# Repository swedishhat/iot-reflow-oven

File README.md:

# iot-reflow-oven
DIY solder reflow ovens. Internet of Toasters. So hot right now.

## Branches

### master
This is where milestone-level code lives. A rule of thumb is that it will always be behind or equal to __dev__ branch. I generally merge changes into master after each documentation article is published

### dev
This is where the action is. I try to make sane commits but continue with caution... thar be dragons.

## Folder Hierarchy

### [doc] Documentation Files
* __01_triac-dimmer__: [Control Your AC Mains with a Microcontroller](http://www.allaboutcircuits.com/projects/controlling-ac-mains-with-a-microcontroller-for-fun-and-profit/)
* __02_atmega-controller__: [Designing Your Own Controller for a Solder Reflow Oven](http://www.allaboutcircuits.com/projects/designing-the-controller-for-a-diy-solder-reflow-oven/)

### [sw] Software Files

#### atmega328p
C files and headers for oven controller

#### esp8266
Either Arduino or NodeMCU files for the controller's web interface

#### python
Scripts for viewing, logging, and interacting with serial data from oven controller

### [hw] Hardware Files

#### most-toast-controller
Contest entry for [Hackaday's](http://hackaday.com/) [Square Inch Project Challenge](http://hackaday.com/2015/10/02/the-square-inch-project-challenges-your-layout-skills/). Small KiCad board containing ATmega328P, MAX31855, headers for ESP-01, thermocouple connector, voltage regulator, and header for CR2032 battery module.

####triac-dimmer
KiCad files for the TRIAC, TRIAC driver circuit, and zero cross detector.

## Attributions
A good chunk of the ATmega328P was modeled after Andy Brown's Bluetooth enabled reflow oven controller. He used and ATmega8 and wrote his project in C++ but a lot of the code is maps pretty easily to C on an ATmega328P. His tutorial page is located [here](http://andybrown.me.uk/2015/07/12/awreflow2/) and his GitHub repository is located [here](https://github.com/andysworkshop/awreflow2/)

The UART code for the ATmega328P was taken from a library writen by [Andy Gock](https://github.com/andygock/avr-uart). It has the added benefit of being generic across numerous AVR platforms and supports multiple UARTs. The library itself contains code from Peter Fleury and others. Andy's license information can be found [here](https://github.com/andygock/avr-uart/blob/master/LICENSE.txt) and there is more complete information located in the uart.h file.

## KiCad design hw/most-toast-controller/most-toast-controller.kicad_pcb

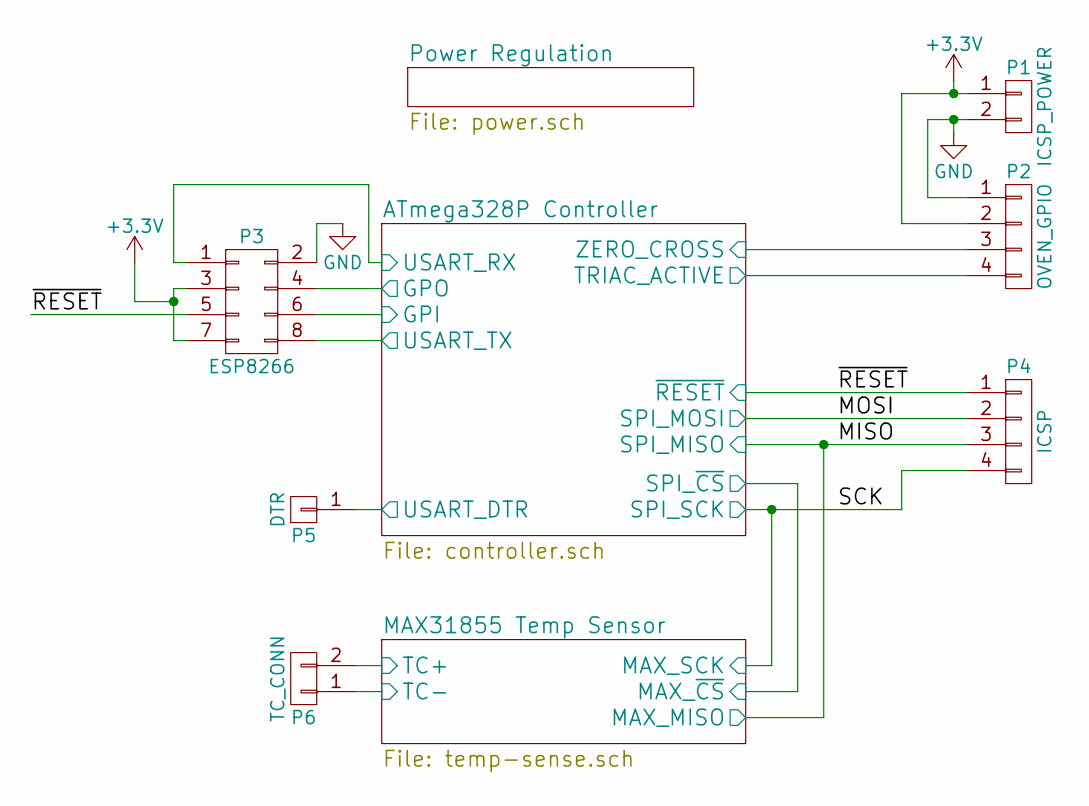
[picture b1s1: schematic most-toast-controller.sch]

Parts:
P1: ICSP_POWER; Pin_Header_Straight_1x02
P2: OVEN_GPIO; Pin_Header_Straight_1x04
P3: ESP8266; Pin_Header_Straight_2x04
P4: ICSP; Pin_Header_Straight_1x04
P5: DTR; Pin_Header_Straight_1x01
P6: TC_CONN; OSTTE020104

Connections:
+3V3: P1.1, P2.2, P3.3, P3.7; also elsewhere on the board
/ATmega328P Controller/GPI: P3.6; also elsewhere on the board
/ATmega328P Controller/GPO: P3.4; also elsewhere on the board
/ATmega328P Controller/SPI_MOSI: P4.2; also elsewhere on the board
/ATmega328P Controller/TRIAC_ACTIVE: P2.4; also elsewhere on the board
/ATmega328P Controller/USART_DTR: P5.1; also elsewhere on the board
/ATmega328P Controller/USART_RX: P3.1; also elsewhere on the board
/ATmega328P Controller/USART_TX: P3.8; also elsewhere on the board
/ATmega328P Controller/ZERO_CROSS: P2.3; also elsewhere on the board
/ATmega328P Controller/~RESET: P3.5, P4.1; also elsewhere on the board
/MAX31855 Temp Sensor/MAX_MISO: P4.3; also elsewhere on the board
/MAX31855 Temp Sensor/MAX_SCK: P4.4; also elsewhere on the board
/MAX31855 Temp Sensor/TC+: P6.2; also elsewhere on the board
/MAX31855 Temp Sensor/TC-: P6.1; also elsewhere on the board
GND: P1.2, P2.1, P3.2; also elsewhere on the board

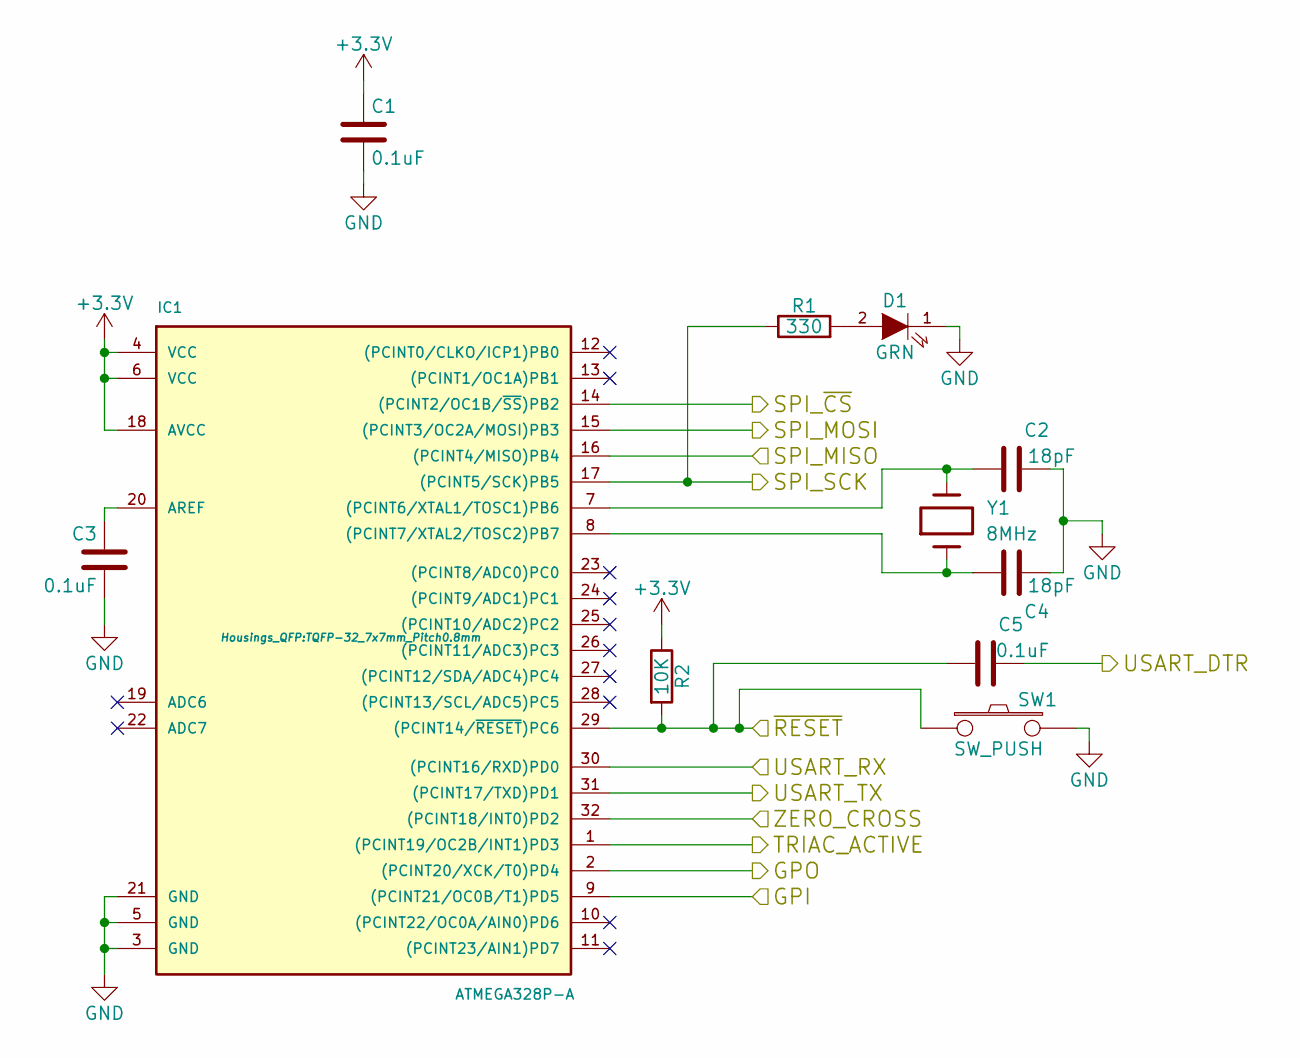
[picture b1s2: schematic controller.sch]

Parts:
C1, C3, C5: 0.1uF; C_0805_HandSoldering
C2, C4: 18pF; C_0805_HandSoldering
D1: GRN; R_0805_HandSoldering
IC1: ATMEGA328P-A; TQFP-32_7x7mm_Pitch0.8mm
R1: 330; R_0805_HandSoldering
R2: 10K; R_0805_HandSoldering
SW1: SW_PUSH; SW_SPST_FSMSM
Y1: 8MHz; Crystal_HC49-SD_SMD

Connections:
+3V3: C1.1, IC1.4 (VCC), IC1.6 (VCC), IC1.18 (AVCC), R2.1; also elsewhere on the board
/ATmega328P Controller/GPI: IC1.9 ((PCINT21/OC0B/T1)PD5); also elsewhere on the board
/ATmega328P Controller/GPO: IC1.2 ((PCINT20/XCK/T0)PD4); also elsewhere on the board
/ATmega328P Controller/SPI_MOSI: IC1.15 ((PCINT3/OC2A/MOSI)PB3); also elsewhere on the board
/ATmega328P Controller/TRIAC_ACTIVE: IC1.1 ((PCINT19/OC2B/INT1)PD3); also elsewhere on the board
/ATmega328P Controller/USART_DTR: C5.2; also elsewhere on the board
/ATmega328P Controller/USART_RX: IC1.30 ((PCINT16/RXD)PD0); also elsewhere on the board
/ATmega328P Controller/USART_TX: IC1.31 ((PCINT17/TXD)PD1); also elsewhere on the board
/ATmega328P Controller/ZERO_CROSS: IC1.32 ((PCINT18/INT0)PD2); also elsewhere on the board
/ATmega328P Controller/~RESET: C5.1, IC1.29 ((PCINT14/~RESET~)PC6), R2.2, SW1.1; also elsewhere on the board
/MAX31855 Temp Sensor/MAX_MISO: IC1.16 ((PCINT4/MISO)PB4); also elsewhere on the board
/MAX31855 Temp Sensor/MAX_SCK: IC1.17 ((PCINT5/SCK)PB5), R1.1; also elsewhere on the board
/MAX31855 Temp Sensor/MAX_~CS: IC1.14 ((PCINT2/OC1B/~SS~)PB2); also elsewhere on the board
GND: C1.2, C2.2, C3.2, C4.2, D1.1 (K), IC1.3 (GND), IC1.5 (GND), IC1.21 (GND), SW1.2; also elsewhere on the board
unnamed: C2.1, IC1.7 ((PCINT6/XTAL1/TOSC1)PB6), Y1.2
unnamed: C3.1, IC1.20 (AREF)
unnamed: C4.1, IC1.8 ((PCINT7/XTAL2/TOSC2)PB7), Y1.1
unnamed: D1.2 (A), R1.2

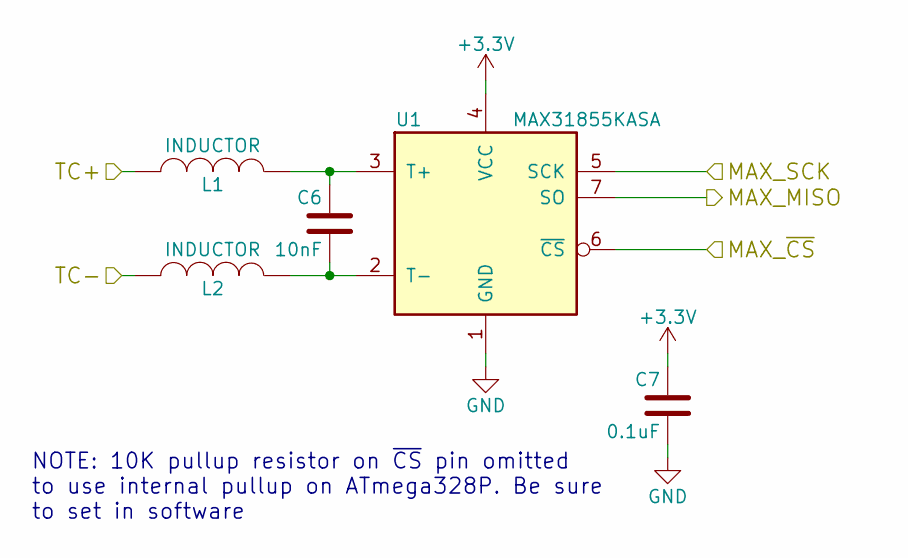
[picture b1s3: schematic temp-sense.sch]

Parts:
C6: 10nF; C_0805_HandSoldering
C7: 0.1uF; C_0805_HandSoldering
L1, L2: INDUCTOR; C_0805_HandSoldering
U1: MAX31855KASA; SOIC-8_3.9x4.9mm_Pitch1.27mm

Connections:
+3V3: C7.1, U1.4 (VCC); also elsewhere on the board
/MAX31855 Temp Sensor/MAX_MISO: U1.7 (SO); also elsewhere on the board
/MAX31855 Temp Sensor/MAX_SCK: U1.5 (SCK); also elsewhere on the board
/MAX31855 Temp Sensor/MAX_~CS: U1.6 (~CS~); also elsewhere on the board
/MAX31855 Temp Sensor/TC+: L1.2; also elsewhere on the board
/MAX31855 Temp Sensor/TC-: L2.2; also elsewhere on the board
GND: C7.2, U1.1 (GND); also elsewhere on the board
unnamed: C6.1, L1.1, U1.3 (T+)
unnamed: C6.2, L2.1, U1.2 (T-)

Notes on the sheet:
NOTE: 10K pullup resistor on ~CS~ pin omitted to use internal pullup on ATmega328P. Be sure to set in software

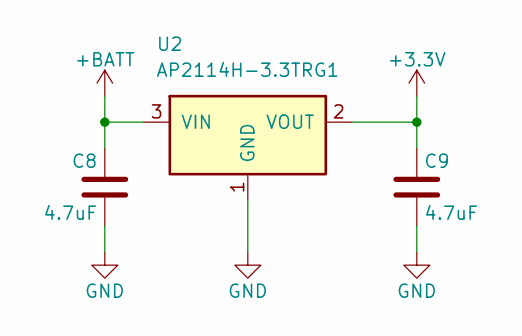
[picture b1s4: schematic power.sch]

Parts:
C8, C9: 4.7uF; C_0805_HandSoldering
U2: AP2114H-3.3TRG1; SOT-223

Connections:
+3V3: C9.1, U2.2 (VOUT); also elsewhere on the board
+BATT: C8.1, U2.3 (VIN)
GND: C8.2, C9.2, U2.1 (GND); also elsewhere on the board

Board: 2 copper layers, 25 parts (5 on the bottom side), 23 nets, no tracks yet.

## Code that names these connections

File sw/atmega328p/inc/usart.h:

// usart.h
#ifndef _USART_H
#define _USART_H

#define USART_BAUD      9600
#define BAUD_PRESCALE   ((((F_CPU / 16) + (USART_BAUD / 2)) / (USART_BAUD)) - 1)      

#define USART_TX        PD1
#define USART_TX_PORT   PORTD
#define USART_TX_DDR    DDRD
#define USART_TX_PIN    PIND

#define USART_RX        PD0
#define USART_RX_PORT   PORTD
#define USART_RX_DDR    DDRD
#define USART_RX_PIN    PIND

/*** USART Initialization Function ***/
void usart_setup(uint32_t ubrr);

/*** USART Flush Function ***/
void usart_flush(void);

/*** USART Transmit Byte Function ***/
void usart_txb(const char data);

/*** USART Print String Function ***/
void usart_print (const char *data);

/*** USART Print String Function with New Line and Carriage Return ***/
void usart_println (const char *data);

#endif

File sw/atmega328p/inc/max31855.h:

/*** max31855.h ***/

#ifndef _MAX31855_H_
#define _MAX31855_H_

/*** GPIO Definitions ***/
#define MAX31855_CS             PB2
#define MAX31855_CS_PORT        PORTB
#define MAX31855_CS_DDR         DDRB
#define MAX31855_CS_PIN         PINB

#define MAX31855_MOSI           PB3
#define MAX31855_MOSI_PORT      PORTB
#define MAX31855_MOSI_DDR       DDRB
#define MAX31855_MOSI_PIN       PINB

#define MAX31855_MISO           PB4
#define MAX31855_MISO_PORT      PORTB
#define MAX31855_MISO_DDR       DDRB
#define MAX31855_MISO_PIN       PINB

#define MAX31855_SCK            PB5
#define MAX31855_SCK_PORT       PORTB
#define MAX31855_SCK_DDR        DDRB
#define MAX31855_SCK_PIN        PINB

/*** Constants ***/
// Status Definitions
#define UNKNOWN                 0
#define OK                      1
#define SCV_FAULT               2
#define SCG_FAULT               3
#define OC_FAULT                4

#define DEFAULT_POLL_INTERVAL   1000    // Read temp probe every second

/*** MAX31855 Device Struct ***/
typedef struct max31855
{
    int16_t     extTemp;        // 14-bit TC temp
    int16_t     intTemp;        // 12-bit internal temp
    uint8_t     status;         // Status flags
    uint32_t    lastTempTime;   // "Timestamp"
    uint32_t    pollInterval;   // Refresh rate of sensor
} max31855;


/*** Temperature Sensor "Object" Constructor ***/
max31855 *max31855_setup(void);

/*** Temperature Sensor Printing Function ***/
void max31855_print(max31855 *tempSense);

/*** Read and Update Temperature Sensor Function ***/
bool max31855_readTempDone(max31855 *tempSense);

/*** Status Message Helper Function ***/
const char *max31855_statusString(uint8_t status);
#endif

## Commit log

2015-11-05 First! Created folder hierarchy and added schems / first round of C code :tada:
2015-11-05 more hw / sw / content. All articles are going to be markdown now... Stupid ass CMS ain't gon ruin my night no mo'git add .!
2015-11-05 Starting porting article to markdown
2015-11-05 Testing markdown doc in github
2015-11-05 All markdown for articles. Images in folder. Just need to flesh out and add more formatting
2015-11-05 Finished article, pending any further revisions
2015-11-05 resize png images
2015-11-05 Changed png to jpg
2015-11-06 Added .gitignore files to sw/ and hw/ and added parts table to dimmer article
2015-11-06 Added video link and cleaned some article stuff up.
2015-11-06 First article published
2015-11-06 Erroneous html thing
2015-11-09 Modularized code, added power correction LUT, new Makefile with lots more features. Codebase ready for first software article.
2015-11-10 msTimer, ovenControl, global macros, and main 'fade' test cleaned up and ready to be expanded on
2015-11-10 Modified gitignore to remove *.out* files (.out.map??) and *.lst files.
2015-11-10 Removed unnecessary files from atmega328p folder
2015-11-11 Added interrupt-driven USART echo mode
2015-11-12 usart, SPI temp sensor, timers, and triac controller all working in perfect harmony. Ready for article writeup.
2015-11-12 updated usart code to remove redundancy / make it mo' modular
2015-11-12 Modified the main.c and oven_control.c files to make a little more sense as far as modularity goes and started drafting readme for article 2
2015-11-12 Added project folder for Hack-a-Day One Inch PCB contest. I call it MostToast
2015-11-13 Added writeup on usart, timer/counters, and oven controller
2015-11-13 Moved around some functions for better modularity / OCD and finished article 2 readme. Needs pictures and maybe some formatting
2015-11-13 added some pictures and finished article
2015-11-13 Final article uploaded and submitted. Ready to merge with master
2015-11-16 most-toast schematic finished.
2015-11-17 Added python script(s) to determine serial ports and allow user to select
2015-11-17 Trying out UART lib with ring buffer and other fun stuff built in.
2015-11-17 Using third party UART library from Andy Gock. Successfully interpreting commands from GNU Screen
2015-11-17 Added credit to README
2015-11-19 Added command interface. Usable for Python testing
2015-11-20 Added step response test python script and data from positive and negative step response test. Got up to 400Cgit add .git add .!
2015-11-23 Finished LUT calculator and moved some things around
2015-11-24 started putting most-toast on a board. Turns out one inch makes for very very small PCB
2015-12-14 First draft of the system characterization article
2015-12-14 added some revision to first draft of article 3
2015-12-26 Added some cmd stuff. Bad commit message, I know...
2015-12-27 Rethinking some ESP <-> AVR comms stuff
